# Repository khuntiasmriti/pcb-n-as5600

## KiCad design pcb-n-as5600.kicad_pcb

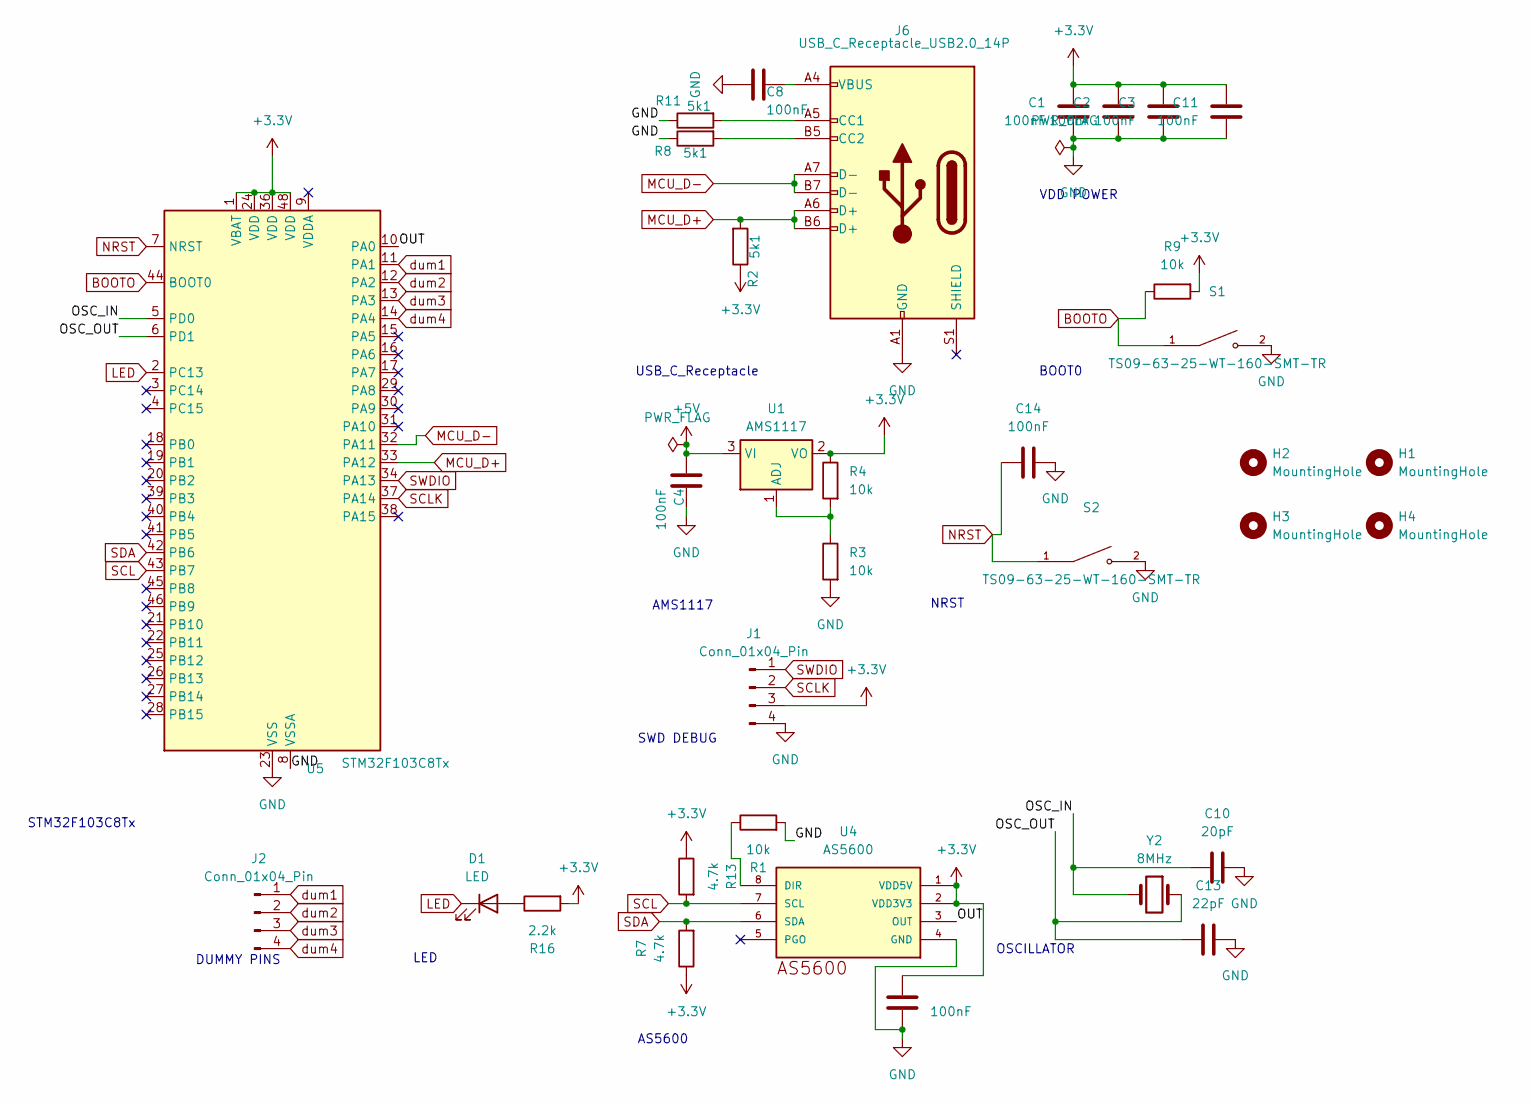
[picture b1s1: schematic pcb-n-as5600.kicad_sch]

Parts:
C1, C2, C3, C4, C7, C8, C11, C14: 100nF; C_0603_1608Metric_Pad1.08x0.95mm_HandSolder
C10: 20pF; C_0603_1608Metric_Pad1.08x0.95mm_HandSolder
C13: 22pF; C_0603_1608Metric_Pad1.08x0.95mm_HandSolder
D1: LED; LED_0603_1608Metric_Pad1.05x0.95mm_HandSolder
H1, H2, H3, H4: MountingHole; MountingHole_3.2mm_M3_Pad
J1, J2: Conn_01x04_Pin; PinSocket_1x04_P2.00mm_Vertical
J6: USB_C_Receptacle_USB2.0_14P; USB_C_Receptacle_GCT_USB4105-xx-A_16P_TopMnt_Horizontal
R1, R3, R4, R9: 10k; R_0603_1608Metric_Pad0.98x0.95mm_HandSolder
R2, R8, R11: 5k1; R_0603_1608Metric_Pad0.98x0.95mm_HandSolder
R7, R13: 4.7k; R_0603_1608Metric_Pad0.98x0.95mm_HandSolder
R16: 2.2k; R_0603_1608Metric_Pad0.98x0.95mm_HandSolder
S1, S2: TS09-63-25-WT-160-SMT-TR; SW_TS09-63-25-WT-160-SMT-TR; PARTREV 1.0
U1: AMS1117; SOT-223-3_TabPin2
U4: AS5600; SOIC8
U5: STM32F103C8Tx; LQFP-48_7x7mm_P0.5mm
Y2: 8MHz; Crystal_SMD_HC49-SD

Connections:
+3.3V: C1.1, C2.1, C3.1, C7.1, C11.1, J1.3, R2.1, R4.1, R7.1, R9.2, R13.1, R16.2, U1.2 (VO), U4.1 (VDD5V), U4.2 (VDD3V3), U5.1 (VBAT), U5.24 (VDD), U5.36 (VDD), U5.48 (VDD)
+5V: C4.1, U1.3 (VI)
/OSC_IN: C10.2, U5.5 (PD0), Y2.2
/OSC_OUT: C13.2, U5.6 (PD1), Y2.1
/OUT: U4.3 (OUT), U5.10 (PA0)
BOOTO: R9.1, S1.1, U5.44 (BOOT0)
GND: C1.2, C2.2, C3.2, C4.2, C7.2, C8.1, C10.1, C11.2, C13.1, C14.1, J1.4, J6.A1 (GND), J6.A12 (GND), J6.B1 (GND), J6.B12 (GND), R1.2, R3.2, R8.1, R11.1, S1.2, S2.2, U4.4 (GND), U5.8 (VSSA), U5.23 (VSS), U5.35 (VSS), U5.47 (VSS)
LED: D1.1 (K), U5.2 (PC13)
MCU_D+: J6.A6 (D+), J6.B6 (D+), R2.2, U5.33 (PA12)
MCU_D-: J6.A7 (D-), J6.B7 (D-), U5.32 (PA11)
NRST: C14.2, S2.1, U5.7 (NRST)
unnamed: C8.2, J6.A4 (VBUS), J6.A9 (VBUS), J6.B4 (VBUS), J6.B9 (VBUS)
unnamed: D1.2 (A), R16.1
unnamed: J6.A5 (CC1), R11.2
unnamed: J6.B5 (CC2), R8.2
unnamed: R3.1, R4.2, U1.1 (ADJ)
unnamed: R1.1, U4.8 (DIR)
SCL: R13.2, U4.7 (SCL), U5.43 (PB7)
SCLK: J1.2, U5.37 (PA14)
SDA: R7.2, U4.6 (SDA), U5.42 (PB6)
SWDIO: J1.1, U5.34 (PA13)
dum1: J2.1, U5.11 (PA1)
dum2: J2.2, U5.12 (PA2)
dum3: J2.3, U5.13 (PA3)
dum4: J2.4, U5.14 (PA4)

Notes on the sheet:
VDD POWER
AMS1117
STM32F103C8Tx
DUMMY PINS
BOOT0
USB_C_Receptacle
LED
NRST
SWD DEBUG
OSCILLATOR
AS5600

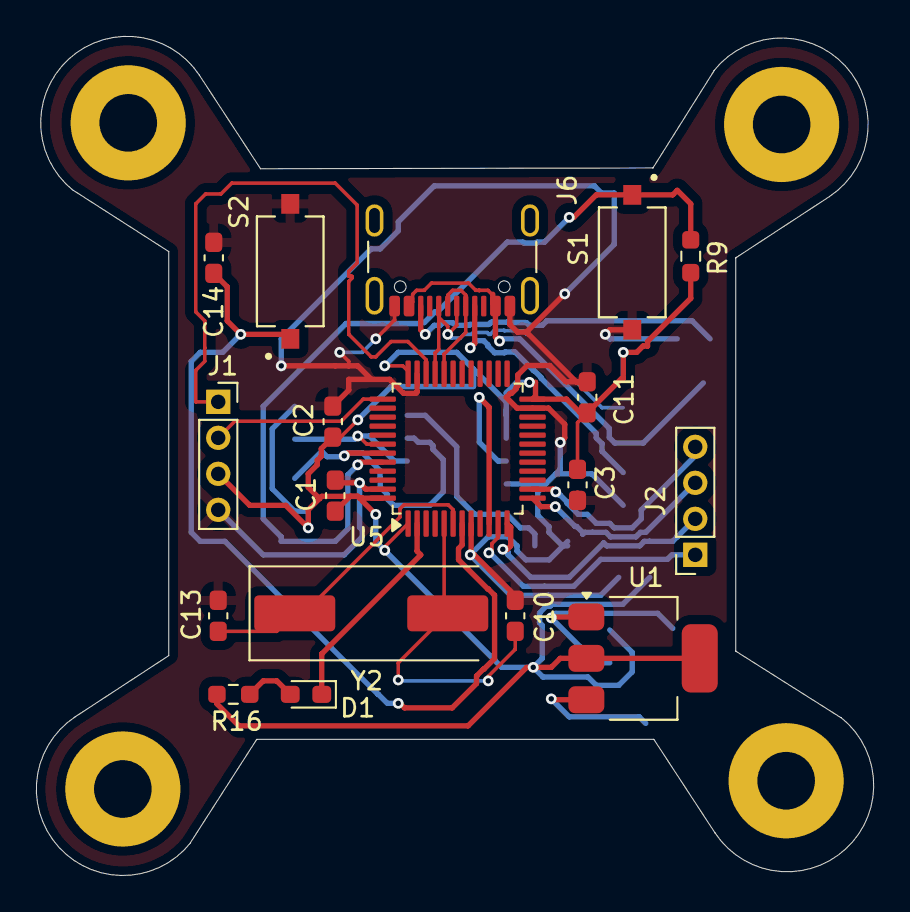
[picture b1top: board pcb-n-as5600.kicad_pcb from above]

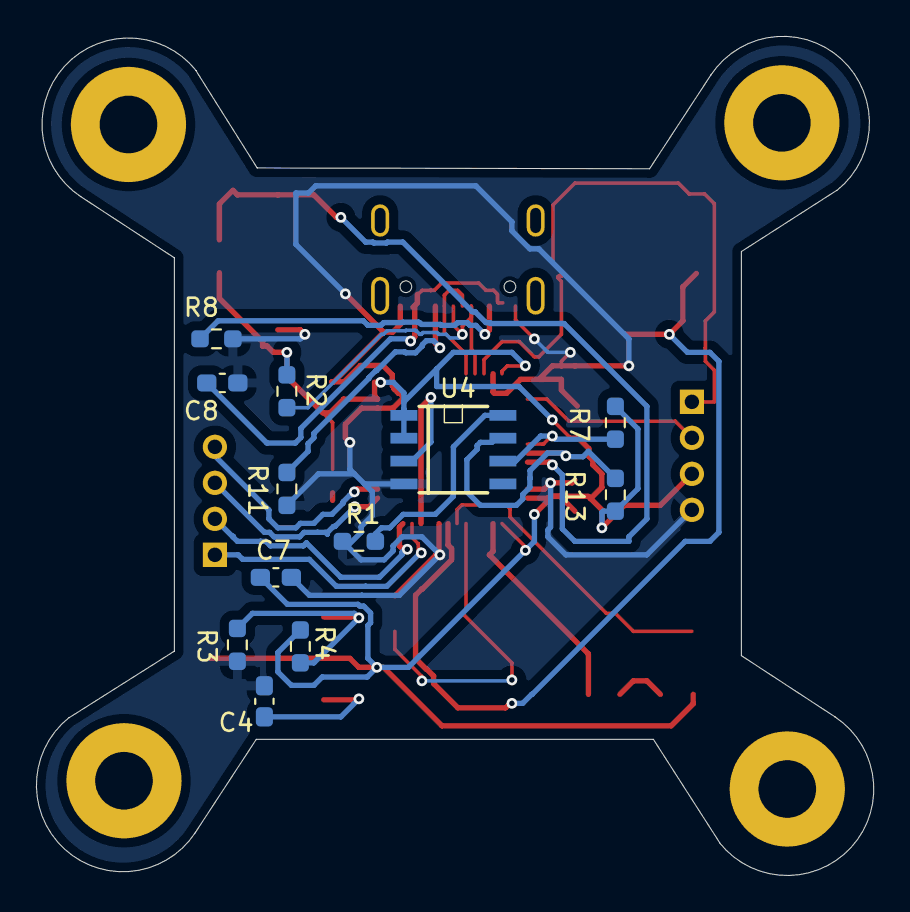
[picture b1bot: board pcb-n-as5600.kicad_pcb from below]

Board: 2 copper layers, 46.5 x 46.6 mm, 34 parts (12 on the bottom side), 25 nets.

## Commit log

2026-02-16 Initial commit - KiCad project
2026-02-17 changes to PCB, schematic
    changed netlist, changed regulator used, changed PCB
2026-02-17 iteration 3
    better wiring, resisistors of devices on bottom instead
2026-02-18 changes toPCB
    changed wiring, zones and position of the resistors and capacitors
2026-02-18 addition of mount holes
    rechecked voltage connections as well, and added
2026-02-18 final pcb with proper connections
    removed UART due to lack of use, connections are correct, slight silk screen issue, final draft
2026-02-19 final with mounting
    changed shape of PCB to accomadate mounting holes
2026-02-19 BOM included
    added BOM for the PCB
2026-02-20 final changes
2026-02-20 changed switch and updated BOM
2026-02-20 final final
